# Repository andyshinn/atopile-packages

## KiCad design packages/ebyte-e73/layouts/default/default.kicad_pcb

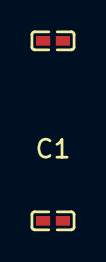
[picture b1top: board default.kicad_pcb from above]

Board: 2 copper layers, 3 parts (0 on the bottom side), 2 nets, no tracks yet.

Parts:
C1, C2: 100nF ±10% 16V X7R; C0402
U1: E73-2G4M08S1CX

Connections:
GND: C1.2, C2.2, U1.5, U1.21, U1.24
power_vdh-VCC: C1.1, C2.1, U1.19, U1.23

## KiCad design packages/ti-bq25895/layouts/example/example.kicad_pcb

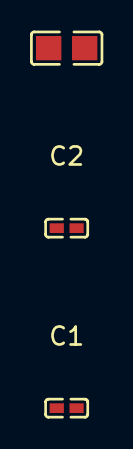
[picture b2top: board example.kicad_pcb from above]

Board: 2 copper layers, 3 parts (0 on the bottom side), 2 nets, no tracks yet.

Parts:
C1: 100nF ±10% 6.3V X7R; C0402
C2: 1µF ±10% 6.3V X5R; C0402
C3: 10µF ±10% 25V X5R; C0805

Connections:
GND: C1.2, C2.2, C3.2
power_regn-VCC: C1.1, C2.1
